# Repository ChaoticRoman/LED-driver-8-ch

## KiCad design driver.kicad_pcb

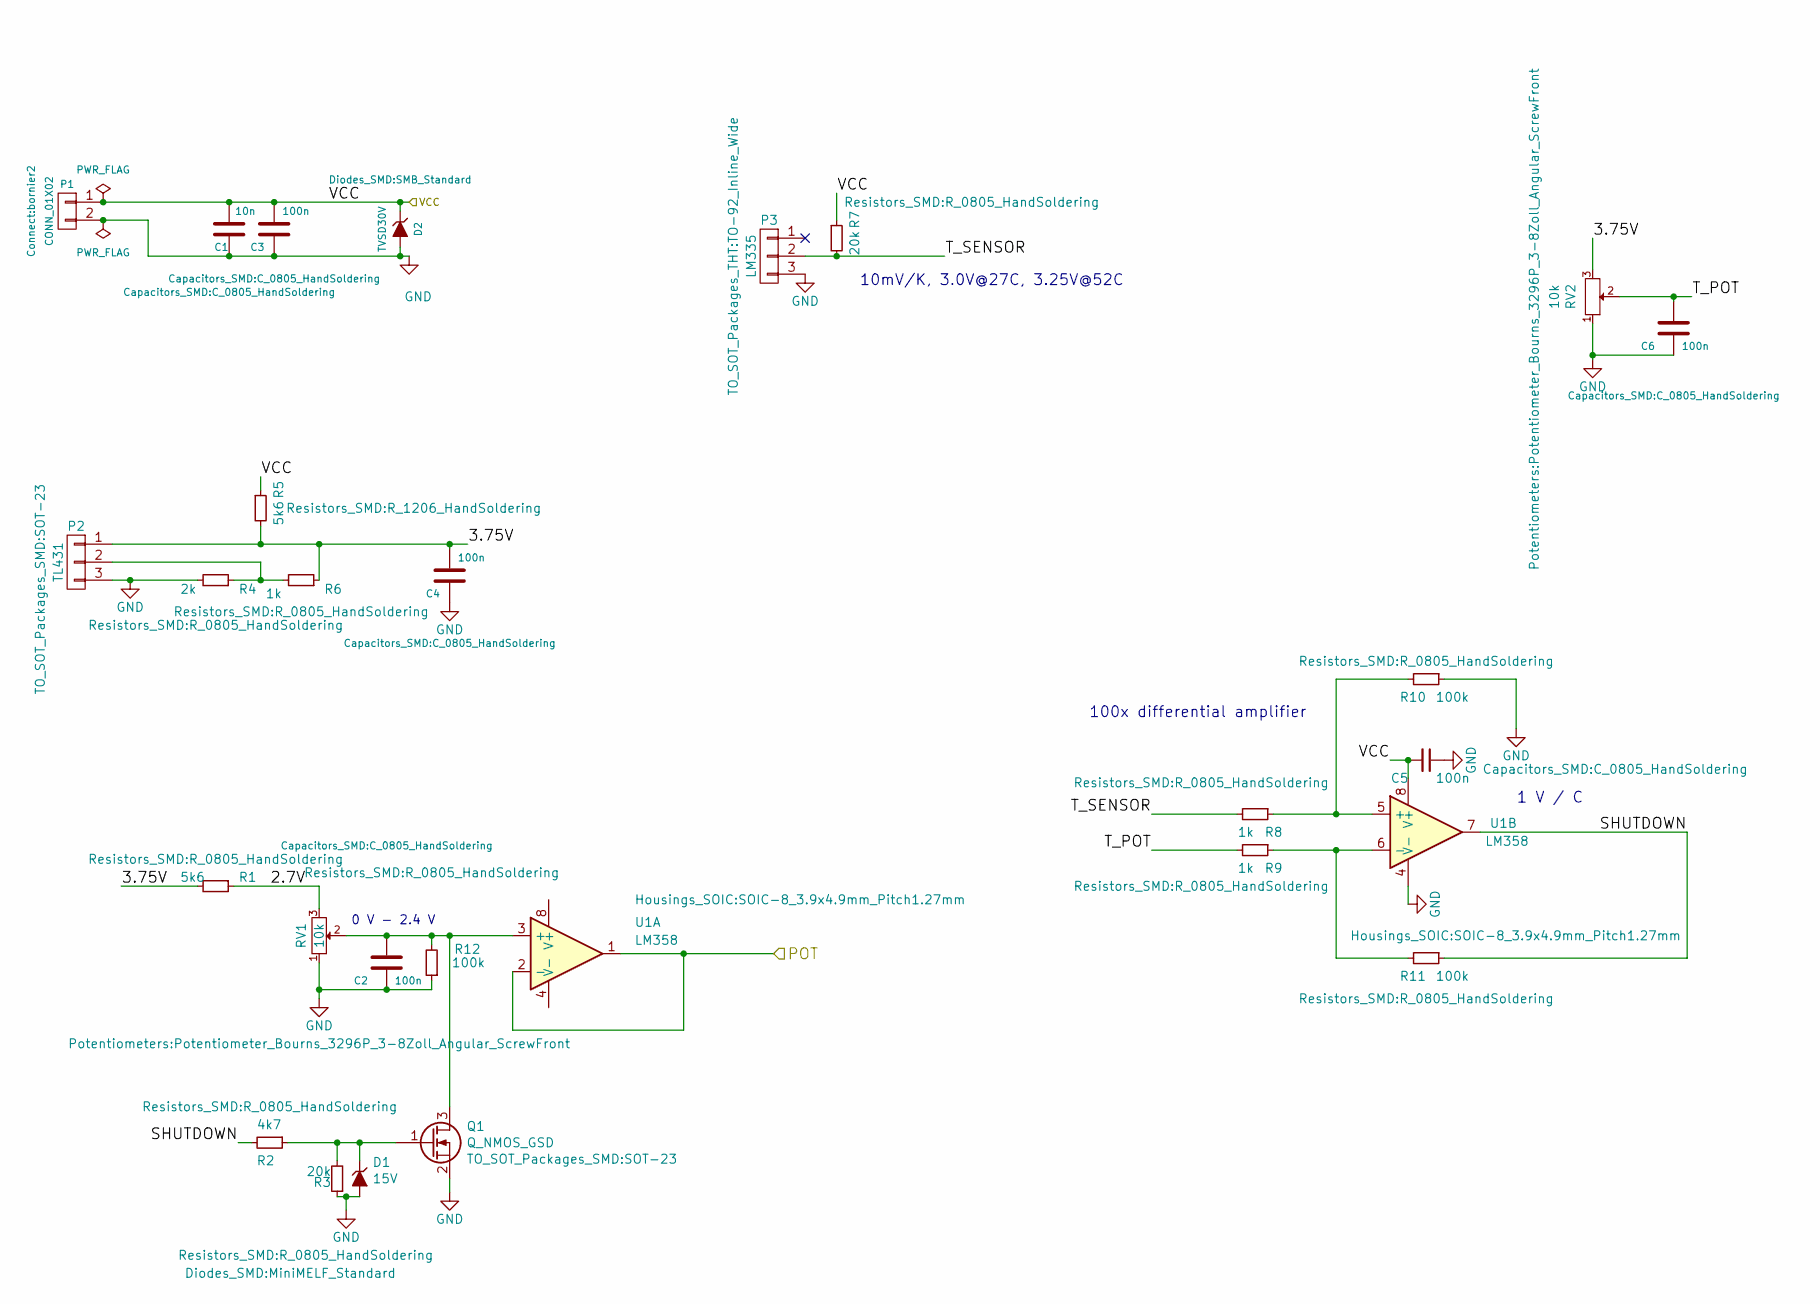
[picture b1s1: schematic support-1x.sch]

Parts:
C1: 10n; C_0805_HandSoldering
C2, C3, C4, C5, C6: 100n; C_0805_HandSoldering
D1: 15V; MiniMELF_Standard
D2: TVSD30V; SMB_Standard
P1: CONN_01X02; bornier2
P2: TL431; SOT-23
P3: LM335; TO-92_Inline_Wide
Q1: Q_NMOS_GSD; SOT-23
R1: 5k6; R_0805_HandSoldering
R2: 4k7; R_0805_HandSoldering
R3, R7: 20k; R_0805_HandSoldering
R4: 2k; R_0805_HandSoldering
R5: 5k6; R_1206_HandSoldering
R6, R8, R9: 1k; R_0805_HandSoldering
R10, R11, R12: 100k; R_0805_HandSoldering
RV1, RV2: 10k; Potentiometer_Bourns_3296P_3-8Zoll_Angular_ScrewFront
U1: LM358; SOIC-8_3.9x4.9mm_Pitch1.27mm

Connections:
/REF: U1.1, U1.2 (-); also elsewhere on the board
/VCC: C1.2, C3.2, C5.2, D2.1 (K), P1.1, R5.1, R7.1, U1.8 (V+); also elsewhere on the board
/support-1x/2.7V: R1.1, RV1.3
/support-1x/3.75V: C4.2, P2.1, R1.2, R5.2, R6.1, RV2.3
/support-1x/SHUTDOWN: R2.2, R11.1, U1.7
/support-1x/T_POT: C6.2, R9.2, RV2.2
/support-1x/T_SENSOR: P3.2, R7.2, R8.2
GND: C1.1, C2.1, C3.1, C4.1, C5.1, C6.1, D1.2 (A), D2.2 (A), P1.2, P2.3, P3.3, Q1.2 (S), R3.1, R4.2, R10.1, R12.1, RV1.1, RV2.1, U1.4 (V-); also elsewhere on the board
unnamed: C2.2, Q1.3 (D), R12.2, RV1.2, U1.3 (+)
unnamed: D1.1 (K), Q1.1 (G), R2.1, R3.2
unnamed: P2.2, R4.1, R6.2
unnamed: R8.1, R10.2, U1.5 (+)
unnamed: R9.1, R11.2, U1.6 (-)

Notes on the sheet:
100x differential amplifier
1 V / C
10mV/K, 3.0V@27C, 3.25V@52C
0 V - 2.4 V

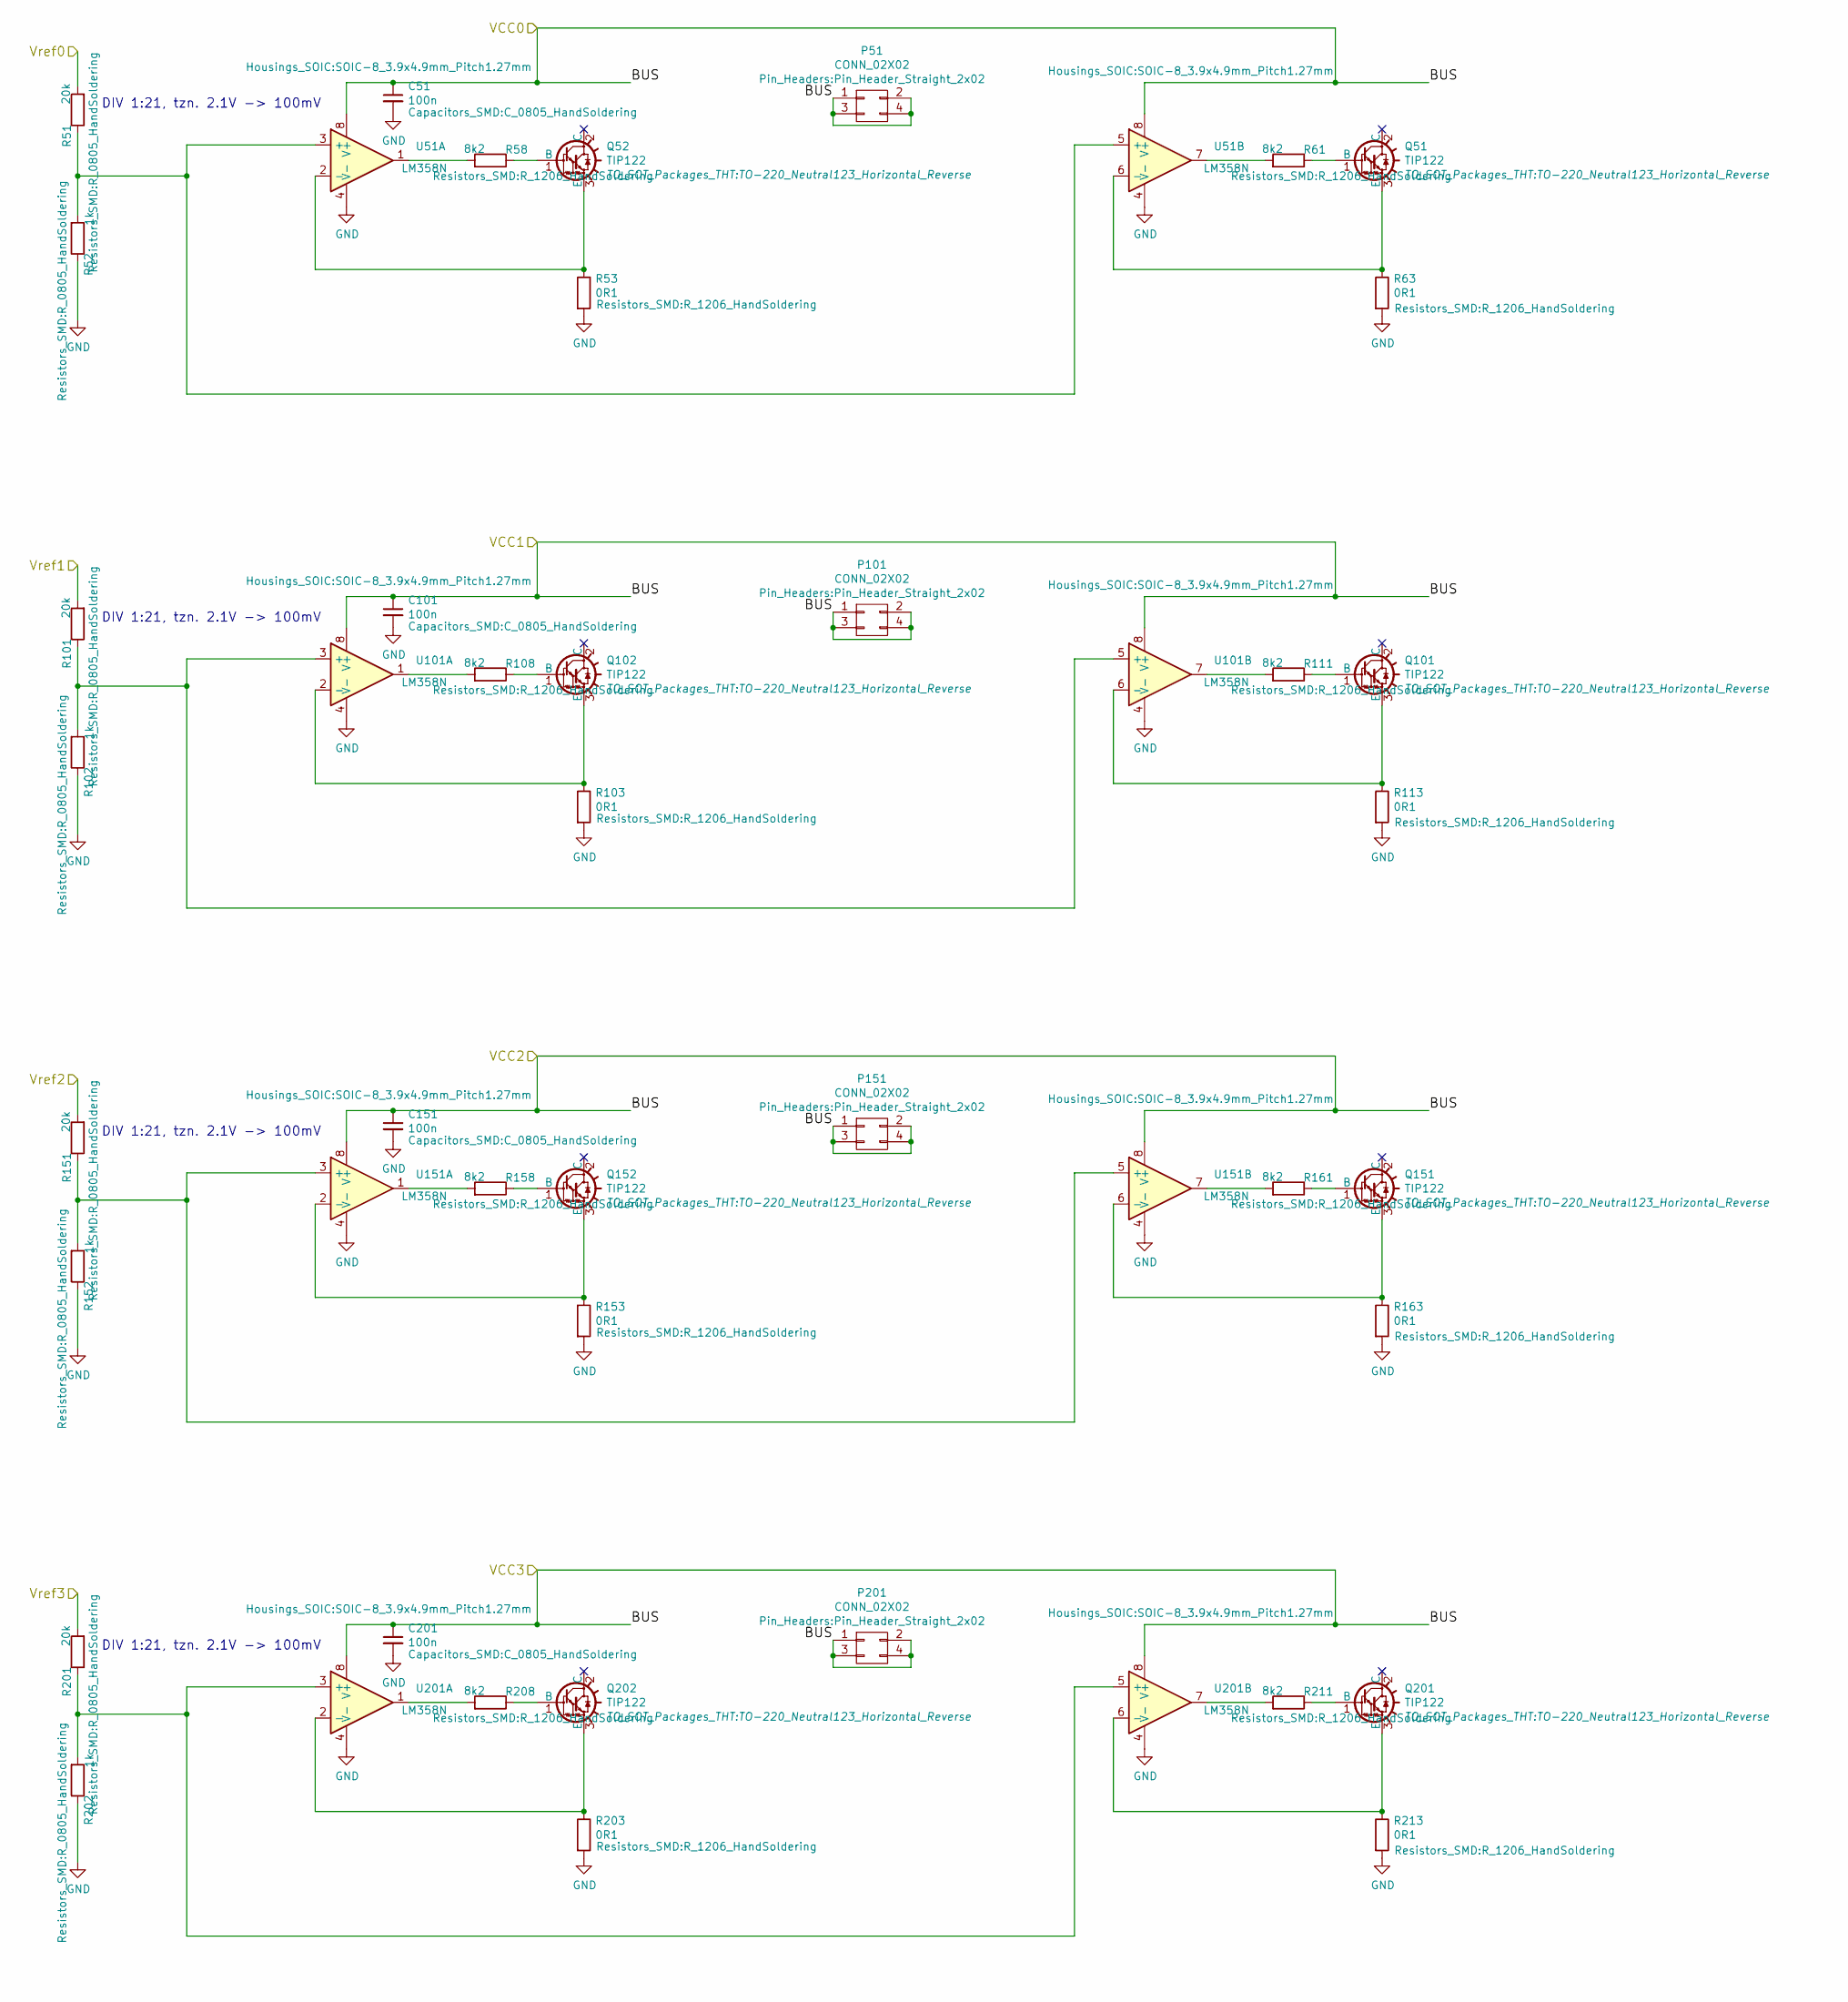
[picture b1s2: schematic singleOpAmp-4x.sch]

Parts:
C51, C101, C151, C201: 100n; C_0805_HandSoldering
P51, P101, P151, P201: CONN_02X02; Pin_Header_Straight_2x02
Q51, Q52, Q101, Q102, Q151, Q152, Q201, Q202: TIP122; TO-220_Neutral123_Horizontal_Reverse
R51, R101, R151, R201: 20k; R_0805_HandSoldering
R52, R102, R152, R202: 1k; R_0805_HandSoldering
R53, R63, R103, R113, R153, R163, R203, R213: 0R1; R_1206_HandSoldering
R58, R61, R108, R111, R158, R161, R208, R211: 8k2; R_1206_HandSoldering
U51, U101, U151, U201: LM358N; SOIC-8_3.9x4.9mm_Pitch1.27mm

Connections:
/REF: R51.2, R101.2, R151.2, R201.2; also elsewhere on the board
/VCC: C51.1, C101.1, C151.1, C201.1, P51.1, P51.2, P51.3, P51.4, P101.1, P101.2, P101.3, P101.4, P151.1, P151.2, P151.3, P151.4, P201.1, P201.2, P201.3, P201.4, U51.8 (V+), U101.8 (V+), U151.8 (V+), U201.8 (V+); also elsewhere on the board
GND: C51.2, C101.2, C151.2, C201.2, R52.1, R53.2, R63.2, R102.1, R103.2, R113.2, R152.1, R153.2, R163.2, R202.1, R203.2, R213.2, U51.4 (V-), U101.4 (V-), U151.4 (V-), U201.4 (V-); also elsewhere on the board
unnamed: Q51.1 (B), R61.1
unnamed: Q51.3 (E), R63.1, U51.6 (-)
unnamed: Q52.1 (B), R58.1
unnamed: Q52.3 (E), R53.1, U51.2 (-)
unnamed: Q101.1 (B), R111.1
unnamed: Q101.3 (E), R113.1, U101.6 (-)
unnamed: Q102.1 (B), R108.1
unnamed: Q102.3 (E), R103.1, U101.2 (-)
unnamed: Q151.1 (B), R161.1
unnamed: Q151.3 (E), R163.1, U151.6 (-)
unnamed: Q152.1 (B), R158.1
unnamed: Q152.3 (E), R153.1, U151.2 (-)
unnamed: Q201.1 (B), R211.1
unnamed: Q201.3 (E), R213.1, U201.6 (-)
unnamed: Q202.1 (B), R208.1
unnamed: Q202.3 (E), R203.1, U201.2 (-)
unnamed: R51.1, R52.2, U51.3 (+), U51.5 (+)
unnamed: R58.2, U51.1
unnamed: R61.2, U51.7
unnamed: R101.1, R102.2, U101.3 (+), U101.5 (+)
unnamed: R108.2, U101.1
unnamed: R111.2, U101.7
unnamed: R151.1, R152.2, U151.3 (+), U151.5 (+)
unnamed: R158.2, U151.1
unnamed: R161.2, U151.7
unnamed: R201.1, R202.2, U201.3 (+), U201.5 (+)
unnamed: R208.2, U201.1
unnamed: R211.2, U201.7

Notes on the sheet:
DIV 1:21, tzn. 2.1V -> 100mV

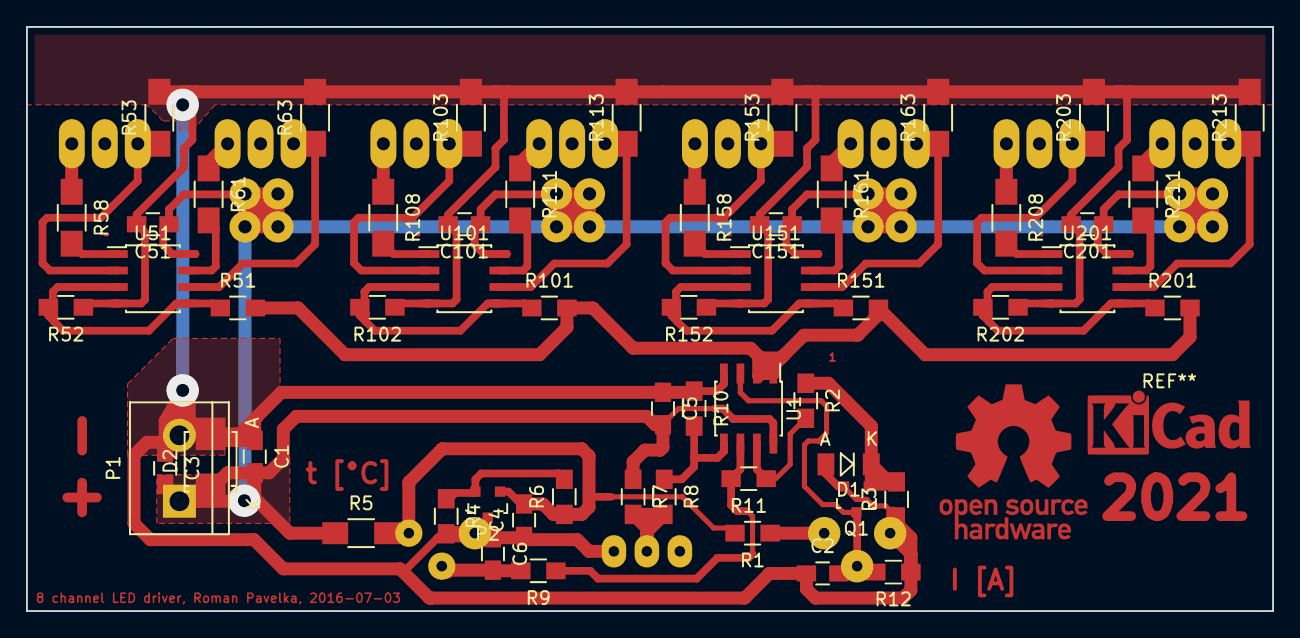
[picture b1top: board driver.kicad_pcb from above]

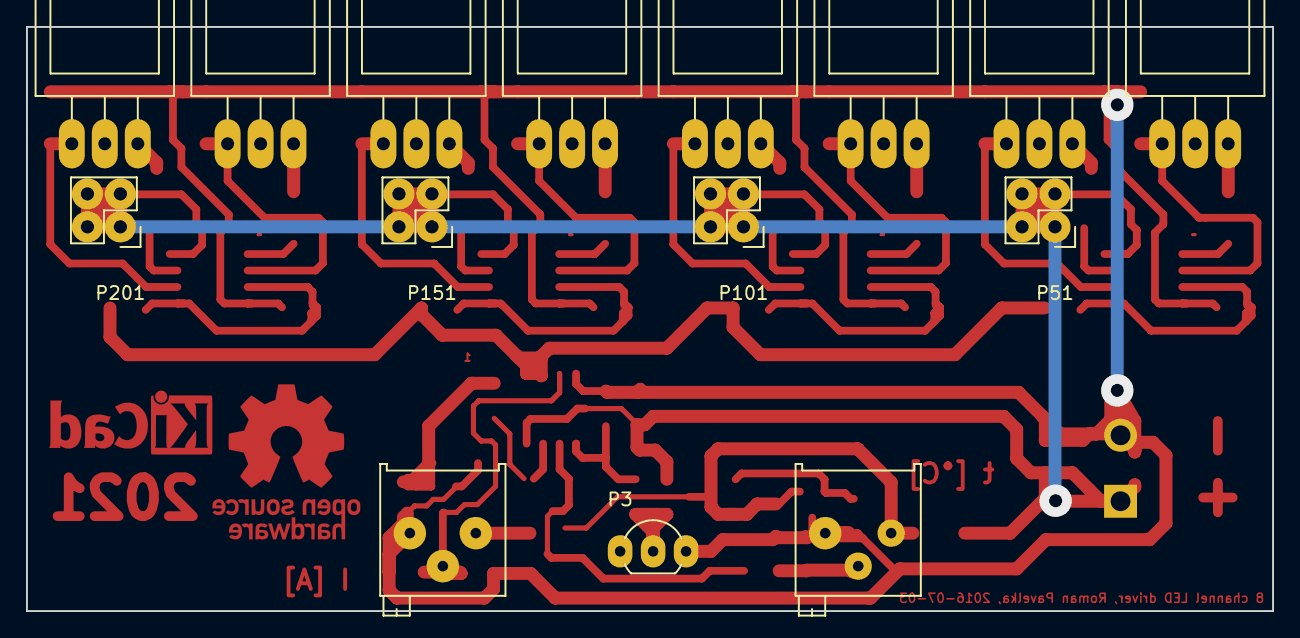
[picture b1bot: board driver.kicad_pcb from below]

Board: 2 copper layers, 96.0 x 45.0 mm, 71 parts (15 on the bottom side), 41 nets.

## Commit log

2021-07-01 Add KiCad .gitignore
2021-07-01 Add 8ch LED driver kicad project
2021-07-01 Few improvements
2021-09-14 Add labels for potentiometers
2021-09-14 Add plot of the latest version
